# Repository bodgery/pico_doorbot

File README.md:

Required libraries:

* Dictionary: https://github.com/arkhipenko/Dictionary
* Tone32: https://github.com/lbernstone/Tone32

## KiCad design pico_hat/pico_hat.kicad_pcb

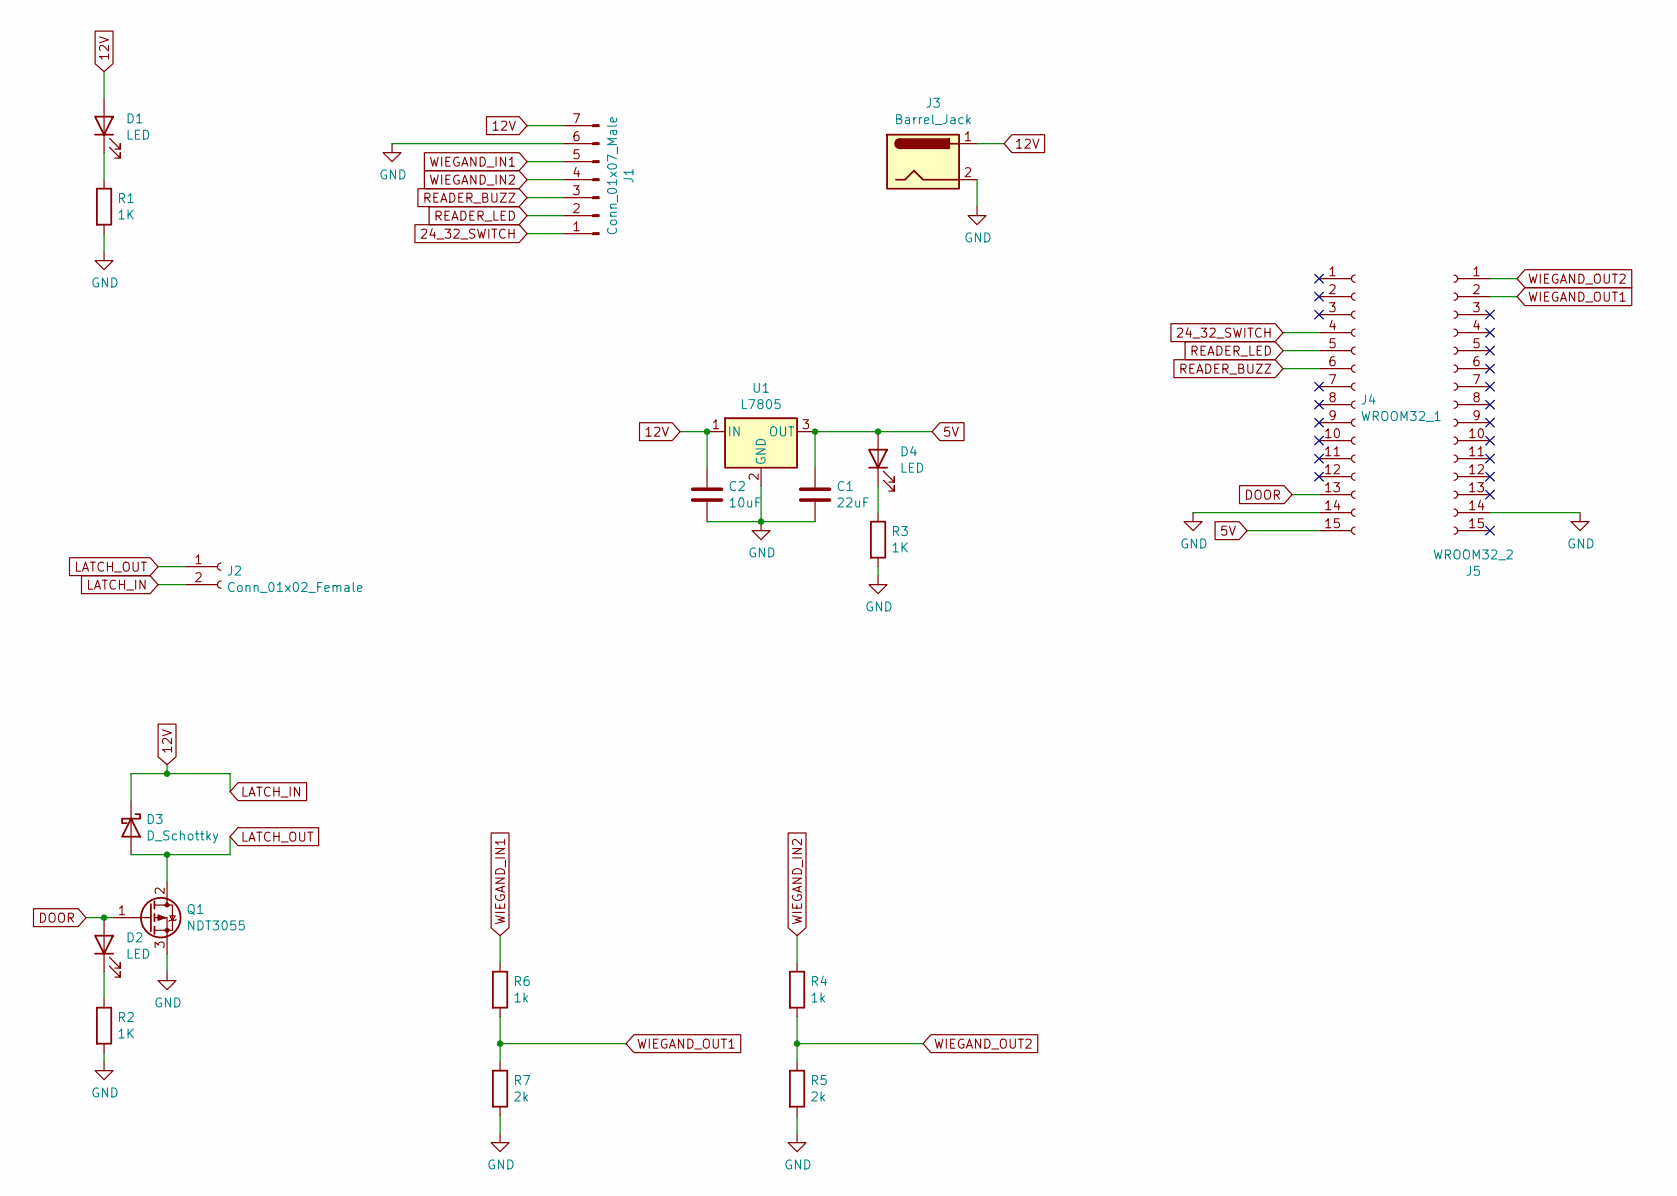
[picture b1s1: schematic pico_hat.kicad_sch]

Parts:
C1: 22uF; C_1206; Digikey # 1276-1771-2-ND
C2: 10uF; C_1206; Digikey # 1276-6736-1-ND
D1: LED; LED-1206; Digikey # 1516-1073-2-N
D2: LED; LED-1206; Digikey # 1516-1072-2-ND
D3: D_Schottky; SMD-1206_Pol; Digikey # 478-7805-2-ND
D4: LED; LED-1206; Digikey # 1516-1076-2-ND
J1: Conn_01x07_Male; Pin_Header_Straight_1x07
J2: Conn_01x02_Female; TerminalBlock_Pheonix_MKDS1.5-2pol; Digikey # ED2561-ND
J3: Barrel_Jack; TerminalBlock_Pheonix_MKDS1.5-2pol; Digikey # ED2561-ND
J4: WROOM32_1; Pin_Header_Straight_1x15
J5: WROOM32_2; Pin_Header_Straight_1x15
Q1: NDT3055; SOT-223; Digikey # NDT3055CT-ND
R1, R2, R3: 1K; R_1210; Digikey # RMCF1210FT1K00
R4, R6: 1k; R_1210; Digikey # RMCF1210FT1K00
R5, R7: 2k; R_1210; Digikey # P2.0KVTR-ND
U1: L7805; TO-220_Neutral123_Vertical; Digikey # 1470-VR10S05-ND

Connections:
5V: C1.1, D4.2 (A), J4.15, U1.3 (OUT)
12V: C2.1, D1.2 (A), D3.1 (K), J1.7, J2.2, J3.1, U1.1 (IN)
24_32_SWITCH: J1.1, J4.4
DOOR: D2.2 (A), J4.13, Q1.1 (G)
GND: C1.2, C2.2, J1.6, J3.2, J4.14, J5.14, Q1.3 (S), R1.2, R2.2, R3.2, R5.2, R7.2, U1.2 (GND)
LATCH_OUT: D3.2 (A), J2.1, Q1.2 (D), Q1.4
unnamed: D1.1 (K), R1.1
unnamed: D2.1 (K), R2.1
unnamed: D4.1 (K), R3.1
READER_BUZZ: J1.3, J4.6
READER_LED: J1.2, J4.5
WIEGAND_IN1: J1.5, R6.1
WIEGAND_IN2: J1.4, R4.1
WIEGAND_OUT1: J5.2, R6.2, R7.1
WIEGAND_OUT2: J5.1, R4.2, R5.1

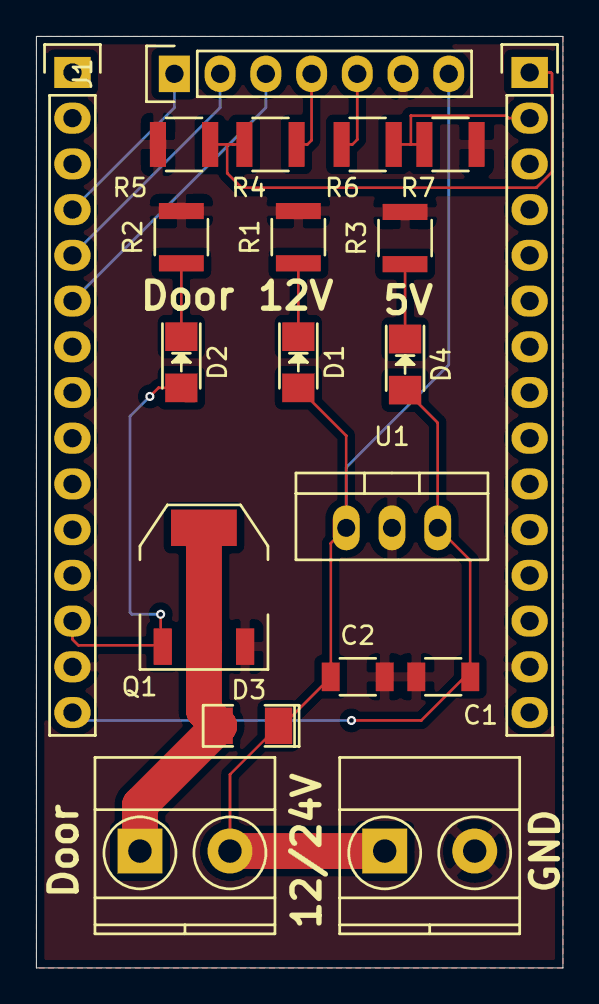
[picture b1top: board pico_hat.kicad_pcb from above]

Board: 2 copper layers, 29.2 x 51.8 mm, 20 parts (0 on the bottom side), 15 nets.

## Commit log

2021-03-05 Add more logging
2021-03-06 Don't need to wait for wifi. Check status code by constant.
2021-03-06 Load JSON into a dictionary for lookup
2021-03-06 Spin off wifi config
2021-03-06 Move user/pass into config
2021-03-06 Rebuild cache on a timer
2021-03-06 Read Wiegand data
2021-03-07 Read from wiegand, lookup key in local cache
2021-03-07 Can lookup keys remotely
2021-03-07 Door open/close
2021-03-27 Switch to a polling method of checking Wiegand
2021-03-28 Wiegand PCB connector
2021-03-31 Use header that attaches to wesp32 board directly
2021-03-31 Add part number for 2x10 pin header
2021-04-23 Change schematic for regular ESP32, not a PoE version
2021-04-24 New layout for regular esp32
2021-04-24 Use larger components. Correct pinout and spacing
2021-07-03 Start on MQTT
2021-07-03 Switch to voltage divider instead of logic level converter
2021-07-20 Voltage dividers
2021-07-26 Ditch MQTT for now
2021-07-27 Move opening the door into success/fail methods
2021-07-27 Log entry of a key, even if we see it in the cache
2021-07-31 Correct door pin
2021-09-10 Take a command for opening door. Correct pinout on MOSFET.
2021-09-17 Add stats command. Add some stuff that was missing in the example config
2021-09-24 Add some extra logging around the JSON parsing. Add request URLs to stats command. Add command to trigger a cache rebuild
2021-09-26 Correct mosfet pinout (for real this time)
2021-09-26 Revert "Correct mosfet pinout (for real this time)"
    This reverts commit 8fe08cf28d7a1d30f1efb70a8aeb7666ade41443.
2021-09-26 Even more pinout corrections
2021-09-26 Use a through-hole buck converter
2021-09-26 Fixup labels
2021-09-28 Script for logging data we get over serial with a timestamp
2021-09-30 Handle cache rebuild errors more gracefully
2021-10-02 New mosfet
2021-11-21 Add help for commands. Add command to check a fob. Reset cache rebuild time even if we fail, so we don't get an infinite loop
2021-11-21 Try playing a tone, though disable it for now
2021-11-25 Use ArudionJSON library rather than Dictionary. Log memory usage.
2024-01-10 Convert to new names
2024-01-11 Add screen pin. Remove two of the three LEDs. Sense input.
2024-01-19 Remove extra LEDs. Connectors for screen and sense input. Move to Pi Pico.

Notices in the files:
pico_hat/pico_hat.kicad_pcb:
Copyright © 2021
